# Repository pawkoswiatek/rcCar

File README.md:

# rcCar

Repository containing hardware schematic and pcb design for a remotely controlled car.

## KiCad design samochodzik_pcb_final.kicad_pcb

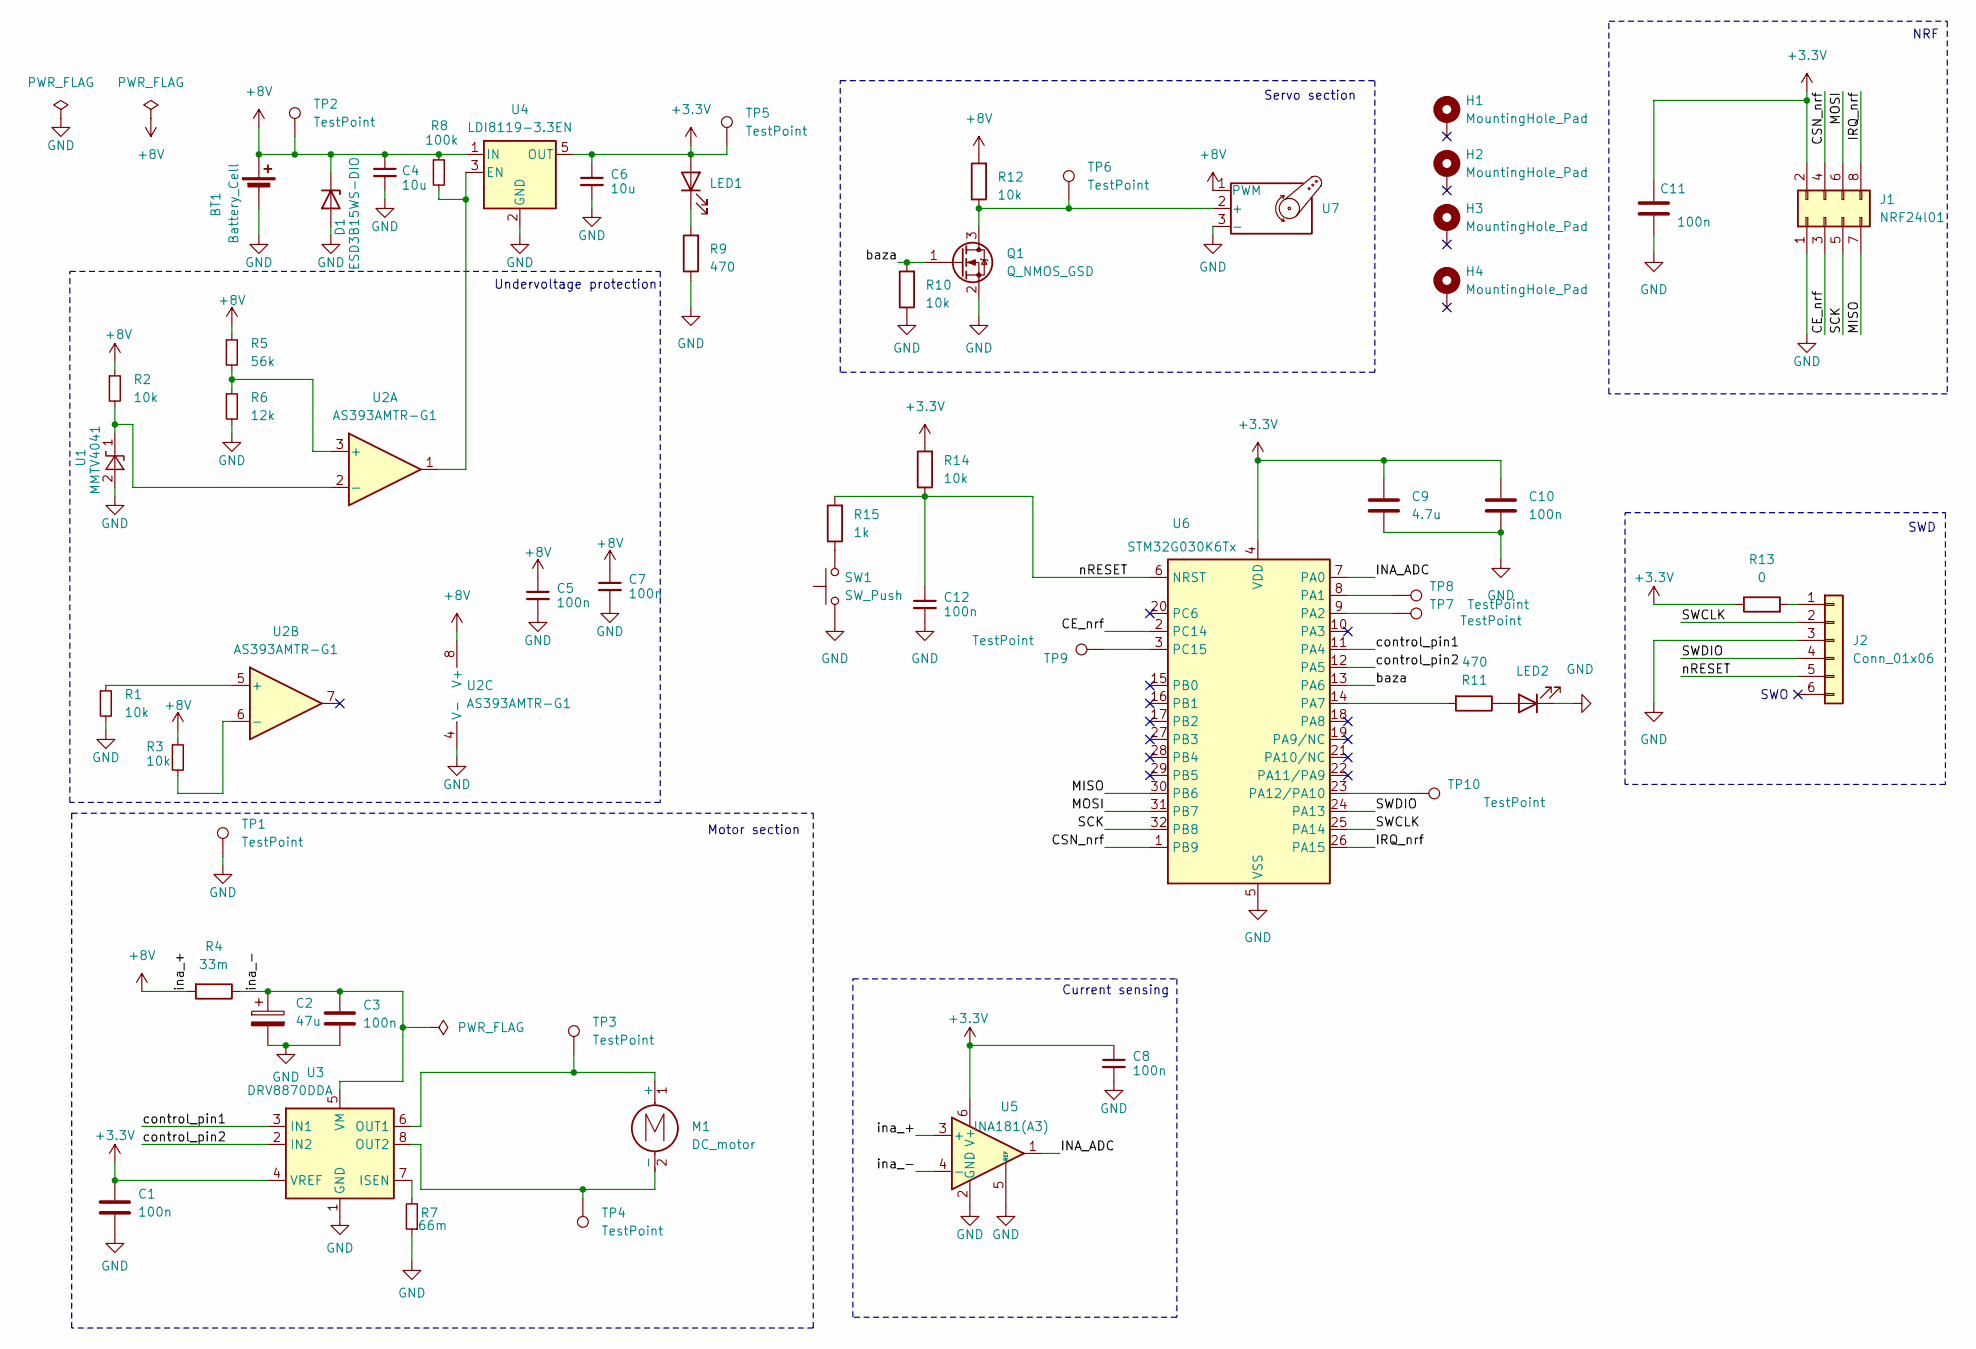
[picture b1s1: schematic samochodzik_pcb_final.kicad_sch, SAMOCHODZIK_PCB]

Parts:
BT1: Battery_Cell; screw_terminal_XY3001V-2P_(5.00)-XINYA
C1, C3, C5, C7, C8, C10, C11, C12: 100n; C_0603_1608Metric
C2: 47u; CP_Elec_6.3x5.3; MPN RC1C476M6L005VR
C4, C6: 10u; C_0603_1608Metric
C9: 4.7u; C_0603_1608Metric
D1: ESD3B15WS-DIO; D_SOD-323_HandSoldering; MPN ESD3B15WS
H1, H2, H3, H4: MountingHole_Pad; MountingHole_3.2mm_M3_DIN965_Pad
J1: NRF24l01; PinHeader_2x04_P2.54mm_Vertical
J2: Conn_01x06; PinHeader_1x06_P2.54mm_Vertical
LED1: LED1; D_0603_1608Metric
LED2: LED2; D_0603_1608Metric
M1: DC_motor; screw_terminal_XY3001V-2P_(5.00)-XINYA
Q1: Q_NMOS_GSD; SOT-23; MPN BXT420N03M
R1, R2, R3, R10, R12, R14: 10k; R_0603_1608Metric
R4: 33m; R_1206_3216Metric; MPN ERJ8CWFR033V
R5: 56k; R_0603_1608Metric
R6: 12k; R_0603_1608Metric
R7: 66m; R_2010_5025Metric; MPN CS10FTGTR068
R8: 100k; R_0603_1608Metric
R9, R11: 470; R_0603_1608Metric
R13: 0; R_0603_1608Metric
R15: 1k; R_0603_1608Metric
SW1: SW_Push; SW_SPST_TL3305A
TP1, TP2, TP3, TP4, TP5, TP6, TP7, TP8, TP9, TP10: TestPoint; TestPoint_Pad_D1.0mm
U1: MMTV4041; SOT-23; MPN MMTV4041
U2: AS393AMTR-G1; SOIC-8_3.9x4.9mm_P1.27mm
U3: DRV8870DDA; Texas_HTSOP-8-1EP_3.9x4.9mm_P1.27mm_EP2.95x4.9mm_Mask2.4x3.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
U4: LDI8119-3.3EN; SOT-23-5
U5: INA181(A3); SOT-23-6
U6: STM32G030K6Tx; LQFP-32_7x7mm_P0.8mm
U7: S1; PinHeader_1x03_P2.54mm_Vertical

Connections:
+3.3V: C1.1, C6.1, C8.1, C9.2, C10.1, C11.2, J1.2, LED1.2 (A), R13.1, R14.2, TP5.1, U3.4 (VREF), U4.5 (OUT), U5.6 (V+), U6.4 (VDD)
+8V: BT1.1 (+), C4.1, C5.1, C7.1, D1.1 (K), R2.1, R3.1, R4.2, R5.1, R8.1, R12.2, TP2.1, U2.8 (V+), U4.1 (IN), U5.3 (+), U7.1 (PWM)
/CE_nrf: J1.3, U6.2 (PC14)
/CSN_nrf: J1.4, U6.1 (PB9)
/INA_ADC: U5.1, U6.7 (PA0)
/IRQ_nrf: J1.8, U6.26 (PA15)
/MISO: J1.7, U6.30 (PB6)
/MOSI: J1.6, U6.31 (PB7)
/SCK: J1.5, U6.32 (PB8)
/SWCLK: J2.2, U6.25 (PA14)
/SWDIO: J2.4, U6.24 (PA13)
/baza: Q1.1 (G), R10.2, U6.13 (PA6)
/control_pin1: U3.3 (IN1), U6.11 (PA4)
/control_pin2: U3.2 (IN2), U6.12 (PA5)
/ina_-: C2.1, C3.1, R4.1, U3.5 (VM), U5.4 (-)
/nRESET: C12.1, J2.5, R14.1, R15.2, U6.6 (NRST)
GND: BT1.2 (-), C1.2, C2.2, C3.2, C4.2, C5.2, C6.2, C7.2, C8.2, C9.1, C10.2, C11.1, C12.2, D1.2 (A), J1.1, J2.3, LED2.1 (K), Q1.2 (S), R1.2, R6.2, R7.1, R9.1, R10.1, SW1.1, TP1.1, U1.2 (A), U2.4 (V-), U3.1 (GND), U3.9 (GND), U4.2 (GND), U5.2 (GND), U5.5 (REF), U6.5 (VSS), U7.3 (-)
unnamed: J2.1, R13.2
unnamed: LED1.1 (K), R9.2
unnamed: LED2.2 (A), R11.1
unnamed: M1.1 (+), TP3.1, U3.6 (OUT1)
unnamed: M1.2 (-), TP4.1, U3.8 (OUT2)
unnamed: Q1.3 (D), R12.1, TP6.1, U7.2 (+)
unnamed: R15.1, SW1.2
unnamed: R2.2, U1.1 (K), U2.2 (-)
unnamed: R5.2, R6.1, U2.3 (+)
unnamed: R1.1, U2.5 (+)
unnamed: R3.2, U2.6 (-)
unnamed: R7.2, U3.7 (ISEN)
unnamed: R8.2, U2.1, U4.3 (EN)
unnamed: TP8.1, U6.8 (PA1)
unnamed: TP7.1, U6.9 (PA2)
unnamed: R11.2, U6.14 (PA7)
unnamed: TP10.1, U6.23 (PA12/PA10)
unnamed: TP9.1, U6.3 (PC15)

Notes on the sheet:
SWD
NRF
SWO
Servo section
Current sensing
Undervoltage protection
Motor section

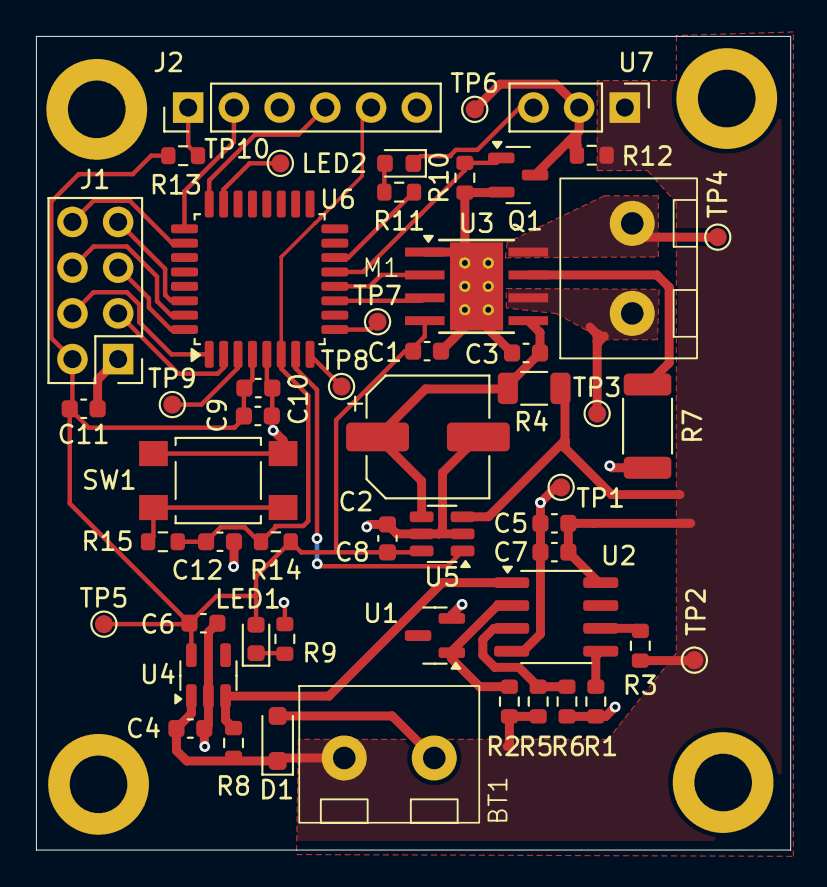
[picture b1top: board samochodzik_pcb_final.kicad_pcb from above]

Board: 2 copper layers, 41.9 x 45.2 mm, 57 parts (0 on the bottom side), 35 nets.

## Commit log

2024-06-20 ostatniaWersja
2024-06-20 readMe
